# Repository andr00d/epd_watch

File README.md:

# epd watch

A low power epaper smartwatch running on an NRF52832.  
It has the basic functionalities like telling time, a stopwatch, and an alarm. But also has some fun features like snake.

## hardware
The kicad files for both the charger and the watch are in the hardware folder. The components in the watch already include LCSC values to order from JLCPCB, but its good to check and make sure every component is still available. Several components will also need to be rotated or moved a bit to ensure correct placement. 

Several extra components are needed, for the display, the GDEW0154M09 is used. The cutout in the PCB is the perfect size for a 202040/202030 battery if you want the biggest batttery possible, but a smaller battery makes soldering easier.

The charger board is a simple PCB to easily connect 4 pogo pins to a pi pico which is flashed with [debugprobe](github.com/raspberrypi/debugprobe). Pogo pins of about 6mm should work best. 

In the 3D_models folder are all the stl files needed to print the cases for both the charger and the watch. To attach the buttons, stick a small bit of tape to the inside of the case and attach the buttons to that, use a bit of glue for a stronger connection. The case for the watch should be able to be made watertight if filled with silicon, but this has not been tested yet. 

## running on the watch
A few steps are needed to be able to compile and run the code on the watch. running the following commands installs cargo embed and the correct target:  
```sudo apt install build-essential```
```rustup target add thumbv7em-none-eabihf```  
```rustup component add llvm-tools```  
```cargo install cargo-binutils```  
```curl --proto '=https' --tlsv1.2 -LsSf https://github.com/probe-rs/probe-rs/releases/latest/download/probe-rs-tools-installer.sh | sh```

After this is finished, just place the watch on the charger and run ```cargo embed``` to flash the watch. if it says it cannot find the programmer, the udev rules might be annoying, follow the instructions on [this page](https://probe.rs/docs/getting-started/probe-setup/), and make sure the watch is making good connection with the programmer.

## running on your pc
There is a pc_test folder that allows additions to the watch to be tested a bit more easily than having to constantly wait for the watch to be programmed. simply go into the pc_test folder, type ```cargo run``` and you can test if everything is as you expect.

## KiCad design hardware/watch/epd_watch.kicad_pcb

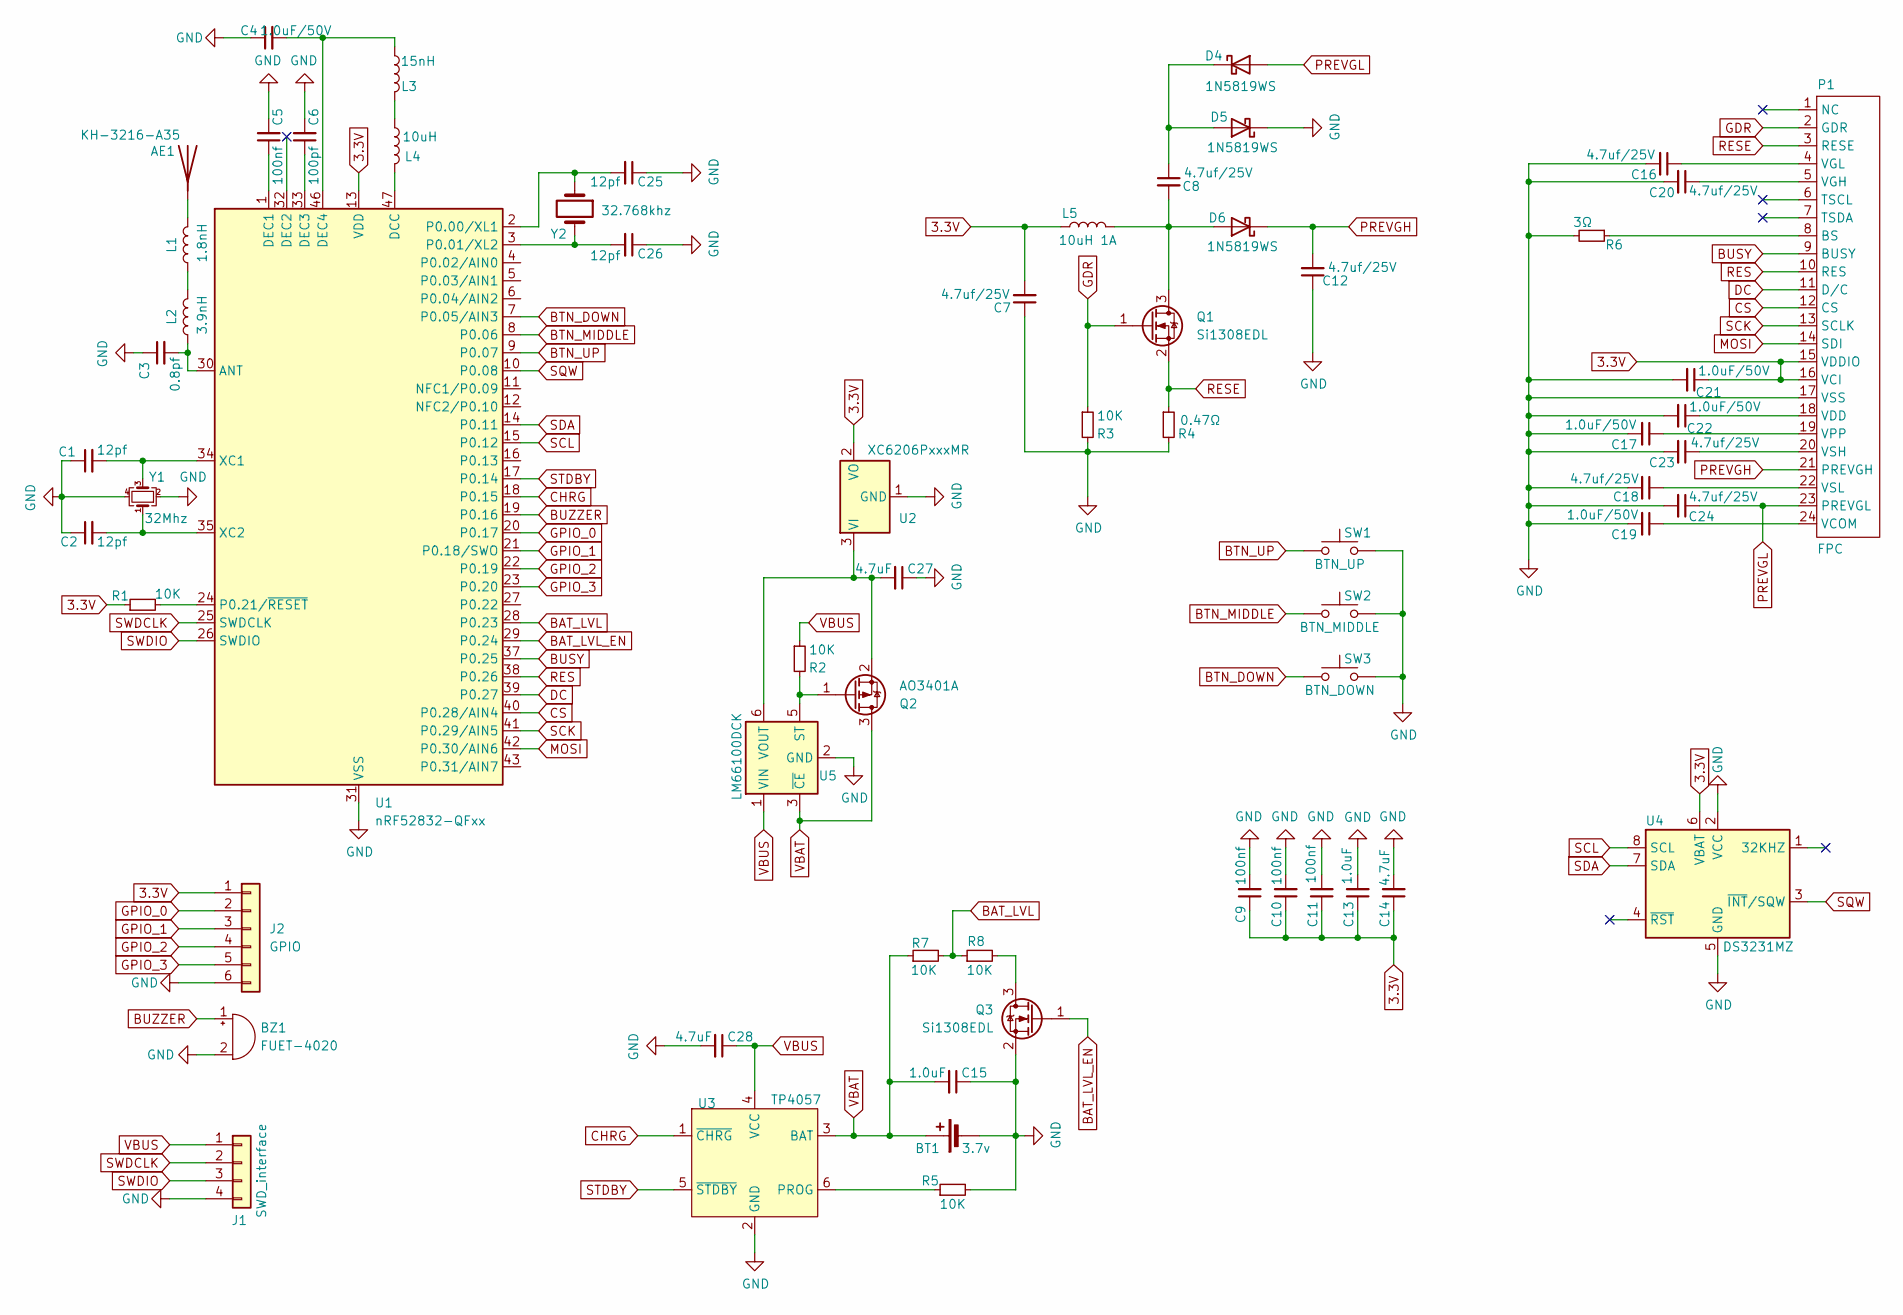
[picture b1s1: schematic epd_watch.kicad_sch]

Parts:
AE1: KH-3216-A35; LCSC C504002
BT1: 3.7v; batt_con
BZ1: FUET-4020; LCSC C391027
C1, C2, C25, C26: 12pf; C_0402_1005Metric; LCSC C161305
C3: 0.8pf; C_0402_1005Metric; LCSC C327032
C4, C17, C19, C21, C22: 1.0uF/50V; C_0402_1005Metric; LCSC C1518208
C5, C9, C10, C11: 100nf; C_0402_1005Metric; LCSC C1525
C6: 100pf; C_0402_1005Metric; LCSC C1546
C7, C8, C12, C16, C18, C20, C23, C24: 4.7uf/25V; C_0402_1005Metric; LCSC C2858031
C13, C15: 1.0uF; C_0402_1005Metric; LCSC C1518208
C14, C27, C28: 4.7uF; C_0402_1005Metric; LCSC C2858031
D4, D5, D6: 1N5819WS; D_SOD-323; LCSC C191023
J1: SWD_interface; pogo_conn
J2: GPIO; gpio_conn
L1: 1.8nH; L_0402_1005Metric; LCSC C703123
L2: 3.9nH; L_0402_1005Metric; LCSC C14033
L3: 15nH; L_0402_1005Metric; LCSC C329619
L4: 10uH; L_0805_2012Metric; LCSC C426327
L5: 10uH 1A; L_0805_2012Metric; LCSC C426327
P1: FPC; FPC-05F-24PH15; LCSC C2856821
Q1, Q3: Si1308EDL; SOT-323_SC-70; LCSC C469327
Q2: AO3401A; SOT-23; LCSC C15127
R1, R2, R3, R5, R7, R8: 10K; R_0402_1005Metric; LCSC C25744
R4: 0.47Ω; R_0402_1005Metric; LCSC C423162
R6: 3Ω; R_0402_1005Metric; LCSC C423196
SW1: BTN_UP; TS-1010A-B; LCSC C381059
SW2: BTN_MIDDLE; TS-1010A-B; LCSC C381059
SW3: BTN_DOWN; TS-1010A-B; LCSC C381059
U1: nRF52832-QFxx; QFN-48-1EP_6x6mm_P0.4mm_EP4.6x4.6mm; LCSC C77540
U2: XC6206PxxxMR; SOT-23-3; LCSC C5446
U3: TP4057; SOT-23-6; LCSC C12044
U4: DS3231MZ; SOIC-8_3.9x4.9mm_P1.27mm; LCSC C107410
U5: LM66100DCK; SOT-363_SC-70-6; LCSC C2869734
Y1: 32Mhz; Crystal_SMD_2016-4Pin_2.0x1.6mm; LCSC C2965582
Y2: 32.768khz; SMD3215; LCSC C32346

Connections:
3.3V: C7.2, C9.1, C10.1, C11.1, C13.1, C14.1, C21.1, J2.1, L5.1, P1.15 (VDDIO), P1.16 (VCI), R1.1, U1.13 (VDD), U1.36 (VDD), U1.48 (VDD), U2.2 (VO), U4.6 (VBAT)
BAT_LVL: R7.2, R8.1, U1.28 (P0.23)
BAT_LVL_EN: Q3.1 (G), U1.29 (P0.24)
BTN_DOWN: SW3.1, U1.7 (P0.05/AIN3)
BTN_MIDDLE: SW2.1, U1.8 (P0.06)
BTN_UP: SW1.1, U1.9 (P0.07)
BUSY: P1.9 (BUSY), U1.37 (P0.25)
BUZZER: BZ1.1 (+), U1.19 (P0.16)
CHRG: U1.18 (P0.15), U3.1 (~CHRG)
CS: P1.12 (CS), U1.40 (P0.28/AIN4)
DC: P1.11 (D/C), U1.39 (P0.27)
GDR: P1.2 (GDR), Q1.1 (G), R3.1
GND: BT1.2 (-), BZ1.2 (-), C1.1, C2.1, C3.1, C4.1, C5.2, C6.2, C7.1, C9.2, C10.2, C11.2, C12.1, C13.2, C14.2, C15.1, C16.2, C17.2, C18.2, C19.2, C20.2, C21.2, C22.2, C23.2, C24.2, C25.1, C26.1, C27.1, C28.2, D5.1 (K), J1.4, J2.6, P1.17 (VSS), Q3.2 (S), R3.2, R4.2, R5.2, R6.2, SW1.2, SW2.2, SW3.2, U1.31 (VSS), U1.45 (VSS), U1.49 (VSS), U2.1 (GND), U3.2 (GND), U4.2 (VCC), U4.5 (GND), U5.2 (GND), Y1.2, Y1.4
GPIO_0: J2.2, U1.20 (P0.17)
GPIO_1: J2.3, U1.21 (P0.18/SWO)
GPIO_2: J2.4, U1.22 (P0.19)
GPIO_3: J2.5, U1.23 (P0.20)
MOSI: P1.14 (SDI), U1.42 (P0.30/AIN6)
unnamed: AE1.1 (A_1), L1.2
unnamed: C8.1, D4.1 (K), D5.2 (A)
unnamed: C8.2, D6.2 (A), L5.2, Q1.3 (D)
unnamed: L1.1, L2.2
unnamed: L3.2, L4.1
unnamed: P1.8 (BS), R6.1
unnamed: C19.1, P1.24 (VCOM)
unnamed: C22.1, P1.18 (VDD)
unnamed: C20.1, P1.5 (VGH)
unnamed: C16.1, P1.4 (VGL)
unnamed: C17.1, P1.19 (VPP)
unnamed: C23.1, P1.20 (VSH)
unnamed: C18.1, P1.22 (VSL)
unnamed: Q2.1 (G), R2.2, U5.5 (ST)
unnamed: C27.2, Q2.2 (S), U2.3 (VI), U5.6 (VOUT)
unnamed: Q3.3 (D), R8.2
unnamed: C3.2, L2.1, U1.30 (ANT)
unnamed: L4.2, U1.47 (DCC)
unnamed: C5.1, U1.1 (DEC1)
unnamed: C6.1, U1.33 (DEC3)
unnamed: C4.2, L3.1, U1.46 (DEC4)
unnamed: C25.2, U1.2 (P0.00/XL1), Y2.1
unnamed: C26.2, U1.3 (P0.01/XL2), Y2.2
unnamed: R1.2, U1.24 (P0.21/~RESET)
unnamed: C1.2, U1.34 (XC1), Y1.3
unnamed: C2.2, U1.35 (XC2), Y1.1
unnamed: R5.1, U3.6 (PROG)
PREVGH: C12.2, D6.1 (K), P1.21 (PREVGH)
PREVGL: C24.1, D4.2 (A), P1.23 (PREVGL)
RES: P1.10 (RES), U1.38 (P0.26)
RESE: P1.3 (RESE), Q1.2 (S), R4.1
SCK: P1.13 (SCLK), U1.41 (P0.29/AIN5)
SCL: U1.15 (P0.12), U4.8 (SCL)
SDA: U1.14 (P0.11), U4.7 (SDA)
SQW: U1.10 (P0.08), U4.3 (~INT/SQW)
STDBY: U1.17 (P0.14), U3.5 (~STDBY)
SWDCLK: J1.2, U1.25 (SWDCLK)
SWDIO: J1.3, U1.26 (SWDIO)
VBAT: BT1.1 (+), C15.2, Q2.3 (D), R7.1, U3.3 (BAT), U5.3 (~CE)
VBUS: C28.1, J1.1, R2.1, U3.4 (VCC), U5.1 (VIN)

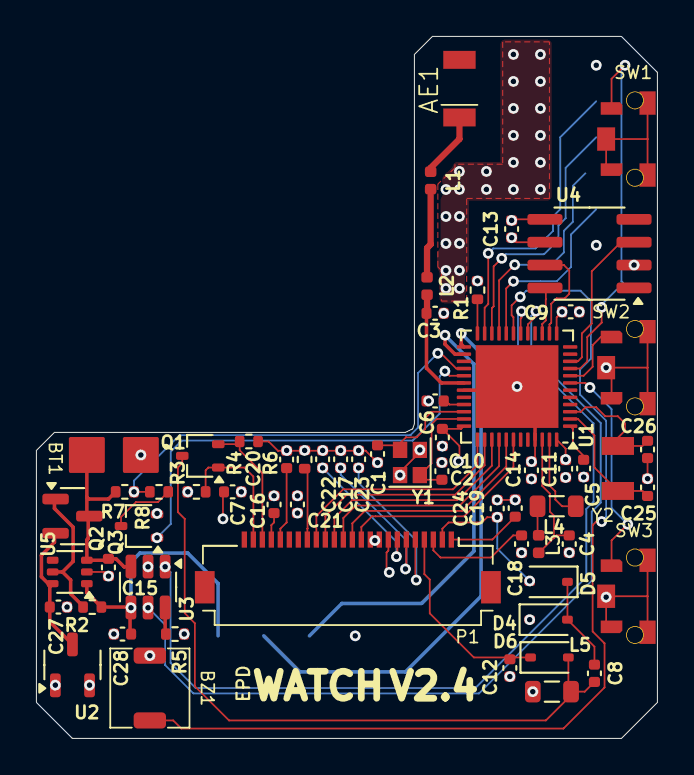
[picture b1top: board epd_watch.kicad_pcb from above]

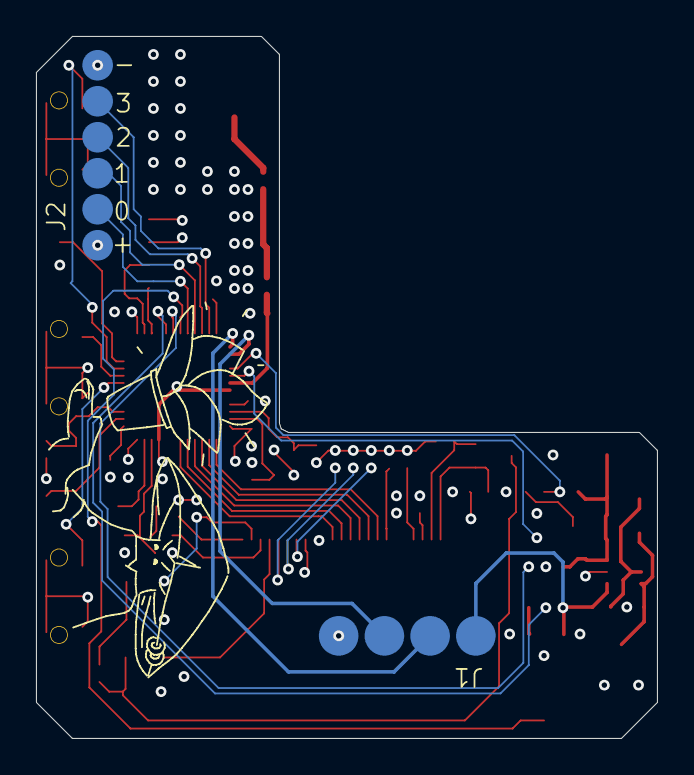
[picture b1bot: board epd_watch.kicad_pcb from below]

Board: 4 copper layers, 34.5 x 39.0 mm, 63 parts (2 on the bottom side), 58 nets.

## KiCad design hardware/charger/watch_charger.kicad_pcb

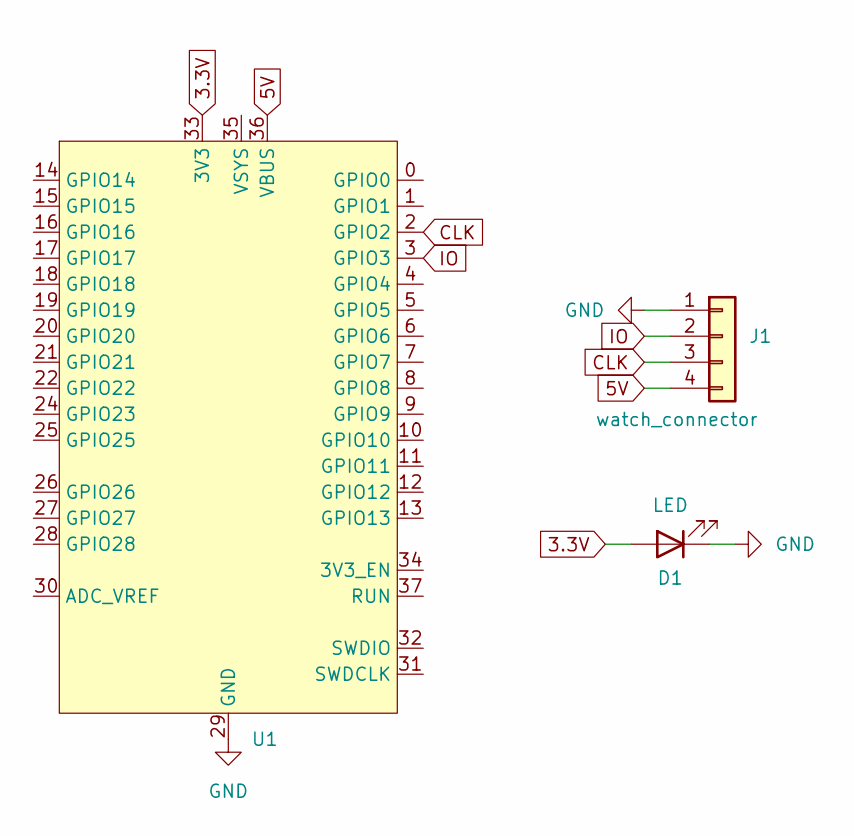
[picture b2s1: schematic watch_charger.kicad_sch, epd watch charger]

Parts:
D1: LED; PinSocket_1x02_P2.54mm_Vertical
J1: watch_connector; PinHeader_1x04_P2.54mm_Vertical
U1: pico

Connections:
3.3V: D1.2 (A), U1.33 (3V3)
5V: J1.4, U1.36 (VBUS)
CLK: J1.3, U1.2 (GPIO2)
GND: D1.1 (K), J1.1, U1.29 (GND)
IO: J1.2, U1.3 (GPIO3)

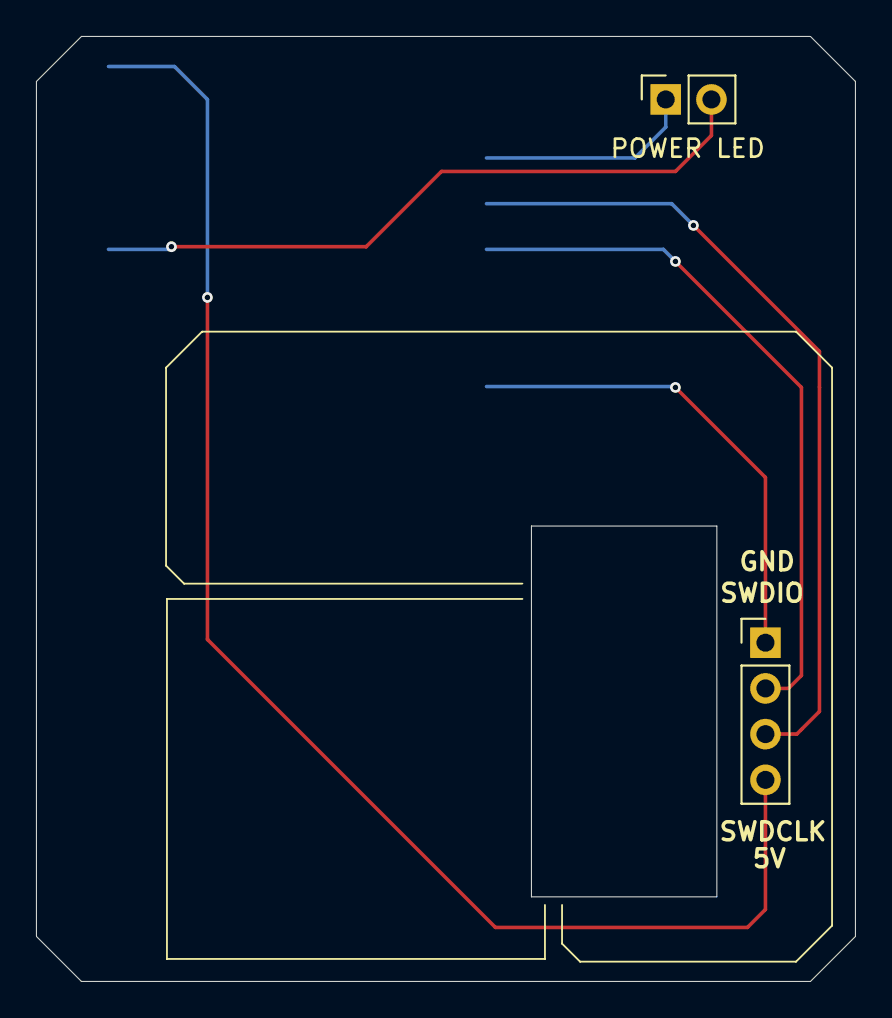
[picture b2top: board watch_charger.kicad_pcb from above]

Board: 2 copper layers, 45.5 x 52.5 mm, 3 parts (1 on the bottom side), 5 nets.

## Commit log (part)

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2024-09-11 dump work so far
2024-10-13 get interrupts working
2024-12-15 display and input works completely
2024-12-24 switched to nrf52832, fixed pc test
2024-12-24 gitignore fix
2024-12-26 finished state machine
2025-01-01 added obligatory snake game
2025-02-20 added hardware files
2025-02-20 forgot a folder
2025-02-25 didnt read datasheet well enough
2025-02-25 fixed bugs and power draw
2025-02-27 removed busy wait
2025-02-28 forgot to update pc test
2025-03-02 added video player
2025-03-17 added sound
2025-03-18 finally implemented stopwatch
2025-03-18 added case stls
2025-03-19 added qr code
2025-03-20 last tweaks for bad apple
2025-04-18 first start at fixing battery measurement and lowering power consumption
2025-04-24 finalized V2.4
2025-05-10 updated code to work for board
2026-04-07 add quick part to make lining up charger easier
